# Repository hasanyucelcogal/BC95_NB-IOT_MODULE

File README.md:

# BC95_NB-IOT_MODULE
BC95 NB-IOT MODULE DESIGN. COMPATIBLE WITH QUECTEL BG96 LPWAN MODULE.

Front

Back

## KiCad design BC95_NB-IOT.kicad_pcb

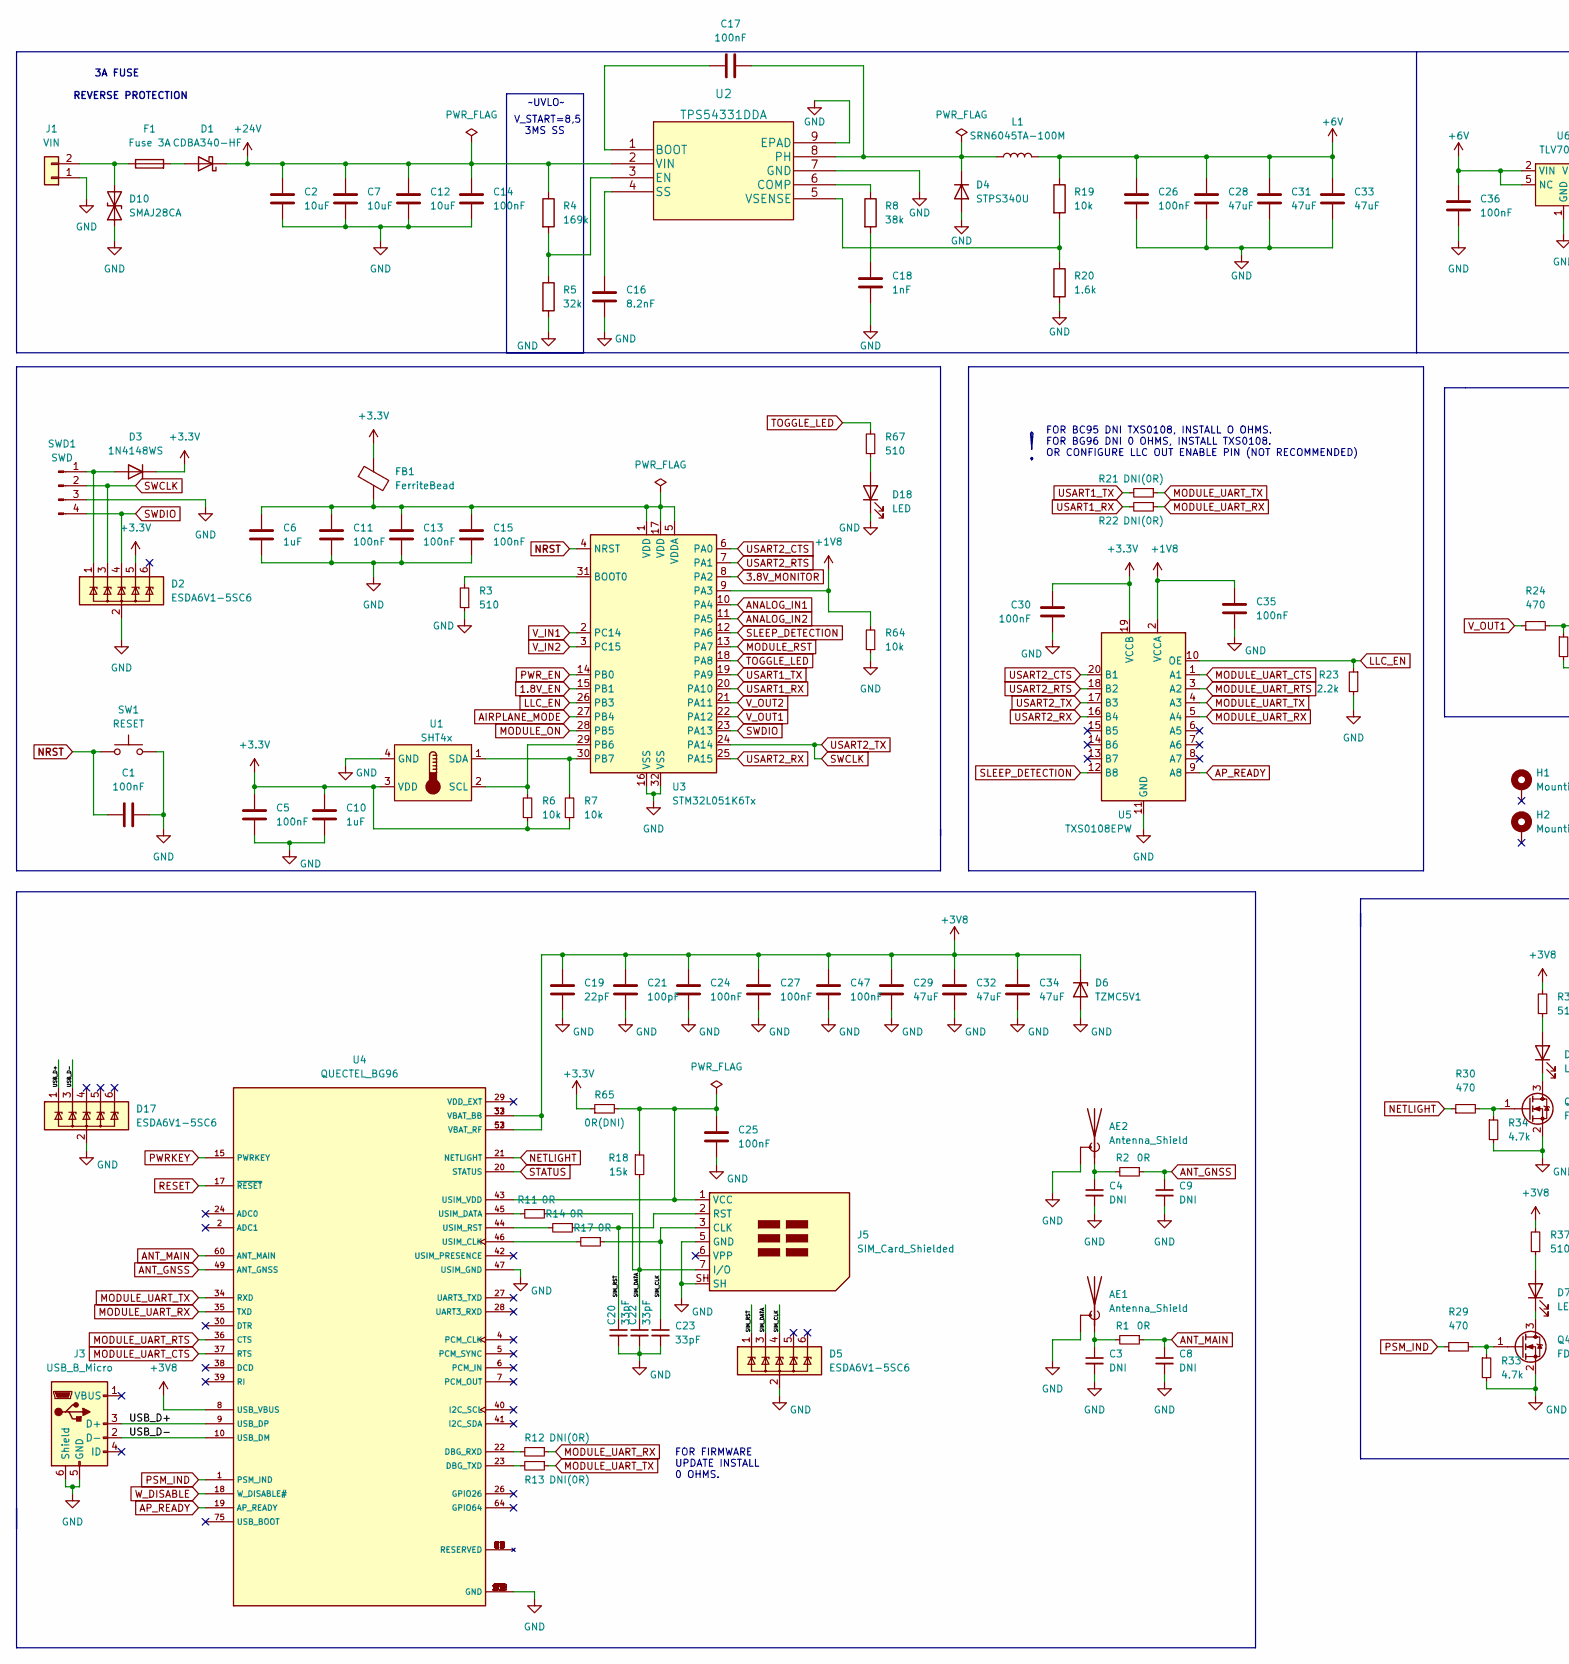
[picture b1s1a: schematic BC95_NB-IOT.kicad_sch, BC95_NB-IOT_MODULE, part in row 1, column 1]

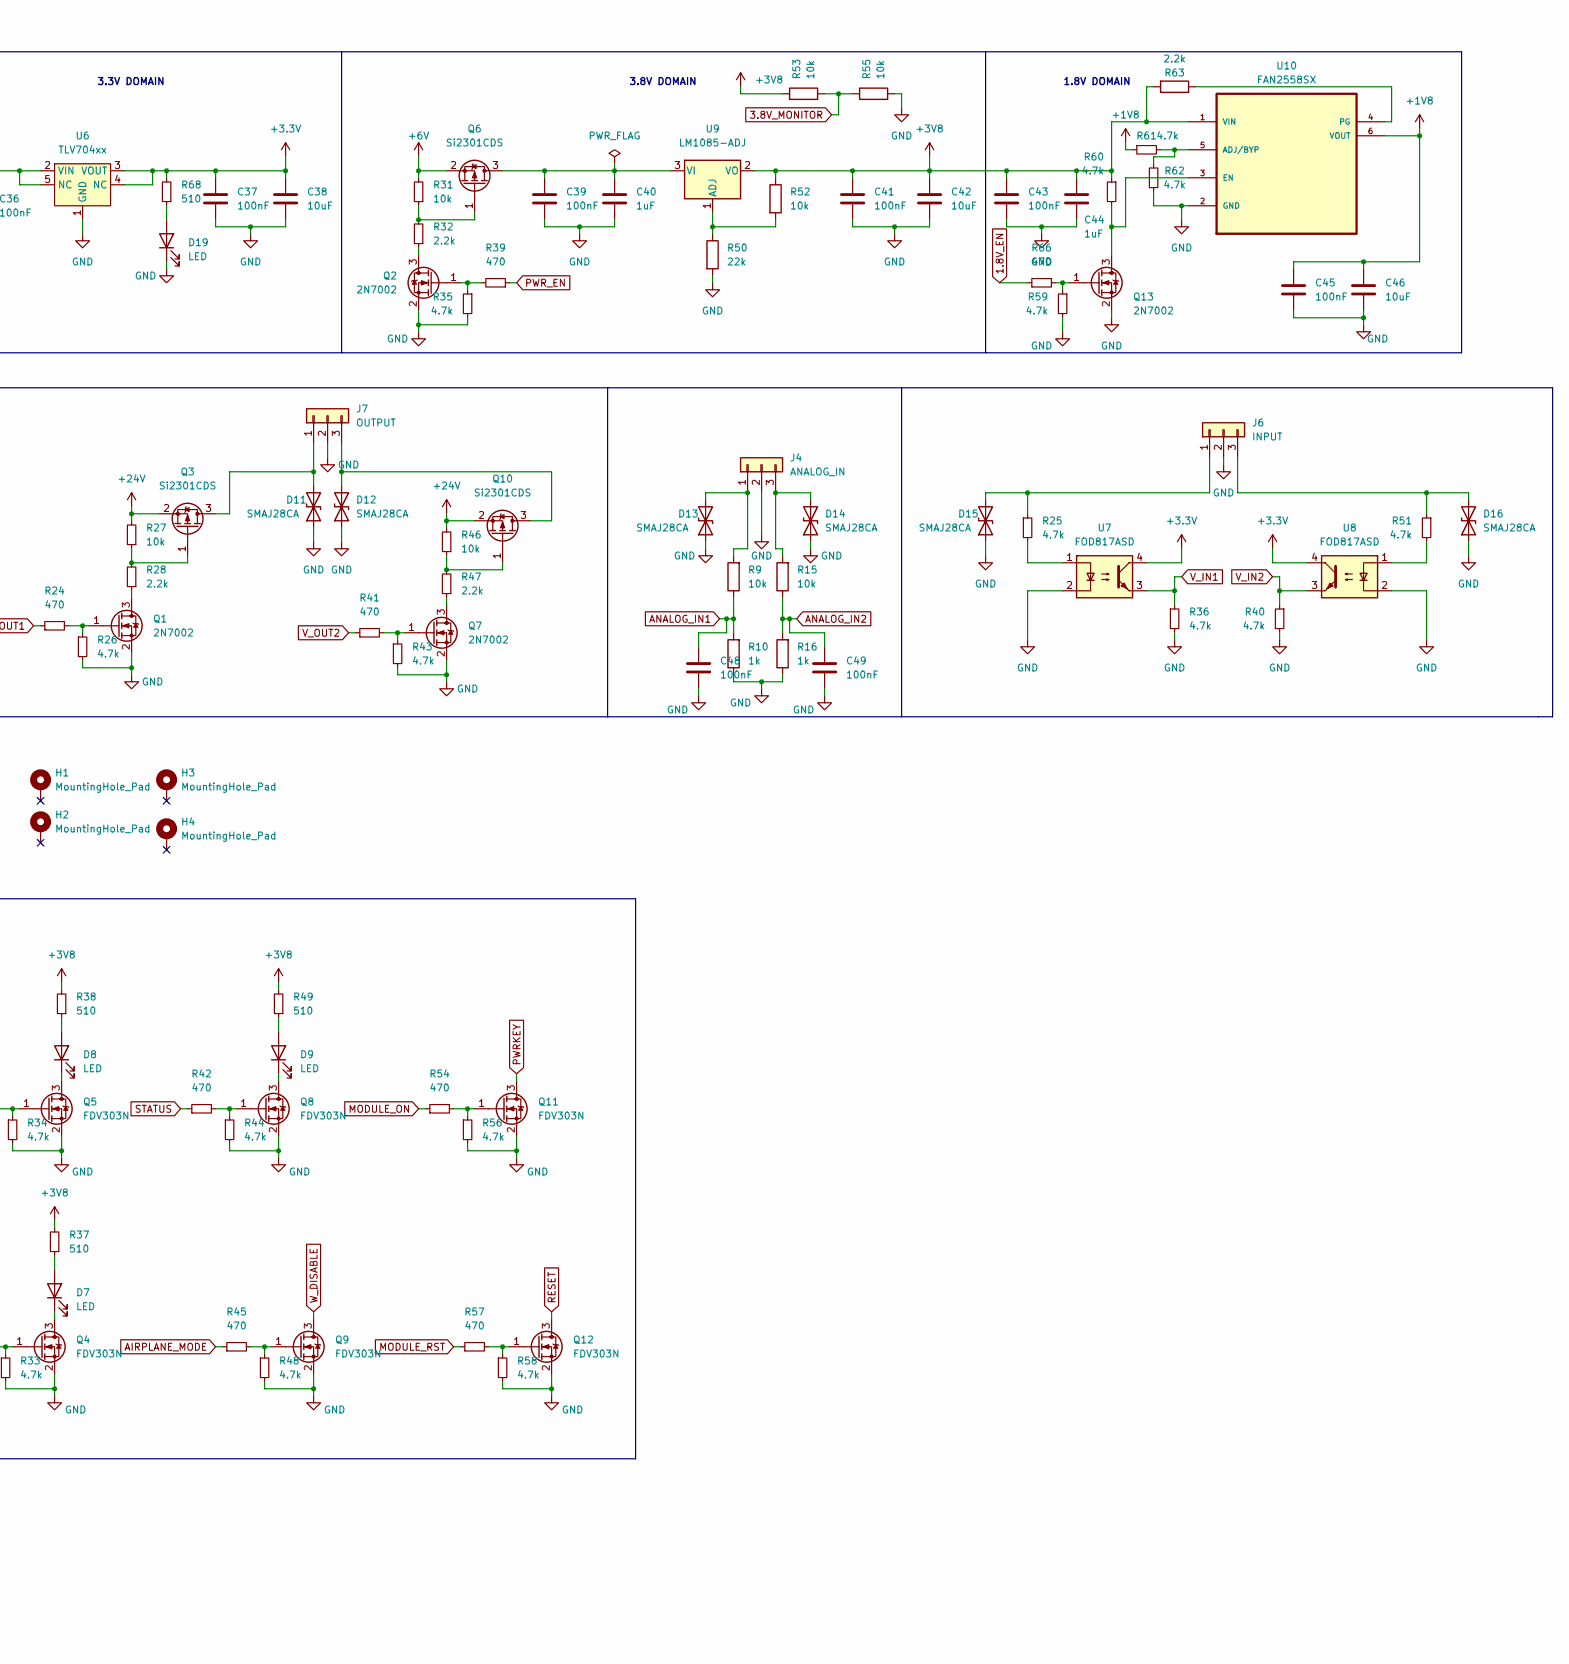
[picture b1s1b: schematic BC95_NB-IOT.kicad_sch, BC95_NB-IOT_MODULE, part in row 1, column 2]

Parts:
AE1, AE2: Antenna_Shield; SMA_Amphenol_901-144_Vertical
C1, C5, C11, C13, C15, C24, C25, C27, C30, C35, C36, C37, C39, C41, C43, C45, C47, C48, C49: 100nF; C_0603_1608Metric
C2, C7, C12: 10uF; C_1206_3216Metric_Pad1.33x1.80mm_HandSolder
C3, C4, C8, C9: DNI; C_0603_1608Metric
C6, C10, C40, C44: 1uF; C_0603_1608Metric
C14, C17, C26: 100nF; C_0603_1608Metric_Pad1.08x0.95mm_HandSolder
C16: 8.2nF; C_0603_1608Metric_Pad1.08x0.95mm_HandSolder
C18: 1nF; C_0603_1608Metric_Pad1.08x0.95mm_HandSolder
C19: 22pF; C_0603_1608Metric
C20, C22, C23: 33pF; C_0603_1608Metric
C21: 100pF; C_0603_1608Metric
C28, C31, C33: 47uF; CP_EIA-3528-21_Kemet-B_Pad1.50x2.35mm_HandSolder
C29, C32, C34: 47uF; CP_EIA-3528-21_Kemet-B
C38, C42, C46: 10uF; CP_EIA-3528-21_Kemet-B
D1: CDBA340-HF; D_SMA
D2, D5, D17: ESDA6V1-5SC6; SOT-23-6
D3: 1N4148WS; D_SOD-323
D4: STPS340U; D_SMB
D6: TZMC5V1; D_MiniMELF
D7, D8, D9, D18, D19: LED; LED_0603_1608Metric
D10, D11, D12, D13, D14, D15, D16: SMAJ28CA; D_SMA
F1: Fuse 3A; Fuse_Littelfuse-NANO2-451_453
FB1: FerriteBead; R_0603_1608Metric
H1, H2, H3, H4: MountingHole_Pad; MountingHole_3.2mm_M3_Pad_Via
J1: VIN; Altech_AK300_1x02_P5.00mm_45-Degree
J3: USB_B_Micro; USB_Micro-B_Molex_47346-0001
J4: ANALOG_IN; PhoenixContact_MC_1,5_3-G-3.81_1x03_P3.81mm_Horizontal
J5: SIM_Card_Shielded; ATTEND_MICRO_SIM
J6: INPUT; PhoenixContact_MC_1,5_3-G-3.81_1x03_P3.81mm_Horizontal
J7: OUTPUT; PhoenixContact_MC_1,5_3-G-3.81_1x03_P3.81mm_Horizontal
L1: SRN6045TA-100M; L_Bourns_SRN6045TA
Q1, Q2, Q7, Q13: 2N7002; SOT-23
Q3, Q6, Q10: Si2301CDS; SOT-23
Q4, Q5, Q8, Q9, Q11, Q12: FDV303N; SOT-23
R1, R2, R11, R14, R17: 0R; R_0603_1608Metric
R3, R37, R38, R49, R67, R68: 510; R_0603_1608Metric
R4: 169k; R_0603_1608Metric_Pad0.98x0.95mm_HandSolder
R5: 32k; R_0603_1608Metric_Pad0.98x0.95mm_HandSolder
R6, R7, R9, R15, R27, R31, R46, R52, R53, R55, R64: 10k; R_0603_1608Metric
R8: 38k; R_0603_1608Metric_Pad0.98x0.95mm_HandSolder
R10, R16: 1k; R_0603_1608Metric
R12, R13, R21, R22: DNI(0R); R_0603_1608Metric
R18: 15k; R_0603_1608Metric
R19: 10k; R_0603_1608Metric_Pad0.98x0.95mm_HandSolder
R20: 1.6k; R_0603_1608Metric_Pad0.98x0.95mm_HandSolder
R23, R28, R32, R47, R63: 2.2k; R_0603_1608Metric
R24, R29, R30, R39, R41, R42, R45, R54, R57, R66: 470; R_0603_1608Metric
R25, R26, R33, R34, R35, R36, R40, R43, R44, R48, R51, R56, R58, R59, R60, R61, R62: 4.7k; R_0603_1608Metric
R50: 22k; R_0603_1608Metric
R65: 0R(DNI); R_0603_1608Metric
SW1: RESET; SW_SPST_B3U-1000P
SWD1: SWD; PinHeader_1x04_P2.54mm_Vertical
U1: SHT4x; SHT4X
U2: TPS54331DDA; TI_SO-PowerPAD-8_ThermalVias
U3: STM32L051K6Tx; LQFP-32_7x7mm_P0.8mm
U4: QUECTEL_BG96; XCVR_BG96
U5: TXS0108EPW; TSSOP-20_4.4x6.5mm_P0.65mm
U6: TLV704xx; SOT-23-5
U7, U8: FOD817ASD; SMDIP-4_W9.53mm
U9: LM1085-ADJ; TO-263-3_TabPin2
U10: FAN2558SX; SOT-23-6

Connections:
1.8V_EN: R66.1, U3.15 (PB1)
3.8V_MONITOR: R53.2, R55.1, U3.8 (PA2)
+1V8: C35.1, C45.1, C46.1, R61.1, R64.2, U3.9 (PA3), U5.2 (VCCA), U10.6 (VOUT)
+3V3: C5.1, C10.1, C30.1, C37.1, C38.1, D2.5 (IO4), D3.1 (K), FB1.1, R6.1, R7.1, R65.1, R68.2, U1.3 (VDD), U5.19 (VCCB), U6.3 (VOUT), U6.4 (NC), U7.4, U8.4
+3V8: C19.1, C21.1, C24.1, C27.1, C29.1, C32.1, C34.1, C41.1, C42.1, C43.1, C44.1, C47.1, D6.1 (K), R37.2, R38.2, R49.2, R52.1, R53.1, R60.1, R63.2, U4.8 (USB_VBUS), U4.32 (VBAT_BB), U4.33 (VBAT_BB), U4.52 (VBAT_RF), U4.53 (VBAT_RF), U9.2 (VO), U10.1 (VIN)
+6V: C26.2, C28.2, C31.2, C33.2, C36.1, L1.2, Q6.2 (S), R19.1, R31.2, U6.2 (VIN), U6.5 (NC)
+24V: C2.1, C7.1, C12.1, C14.2, D1.1 (K), Q3.2 (S), Q10.2 (S), R4.1, R27.2, R46.2, U2.2 (VIN)
/SIM_CLK: C23.1, D5.4 (IO3), J5.3 (CLK), R17.1
/SIM_DATA: C22.1, D5.3 (IO2), J5.7 (I/O), R11.1, R18.2
/SIM_RST: C20.1, D5.1 (IO1), J5.2 (RST), R14.1
/USB_D+: D17.1 (IO1), J3.3 (D+), U4.9 (USB_DP)
/USB_D-: D17.3 (IO2), J3.2 (D-), U4.10 (USB_DM)
AIRPLANE_MODE: R45.1, U3.27 (PB4)
ANALOG_IN1: C48.1, R9.1, R10.2, U3.10 (PA4)
ANALOG_IN2: C49.1, R15.1, R16.2, U3.11 (PA5)
ANT_GNSS: C9.1, R2.1, U4.49 (ANT_GNSS)
ANT_MAIN: C8.1, R1.1, U4.60 (ANT_MAIN)
AP_READY: U4.19 (AP_READY), U5.9 (A8)
GND: AE1.2 (Shield), AE2.2 (Shield), C1.2, C2.2, C3.2, C4.2, C5.2, C6.2, C7.2, C8.2, C9.2, C10.2, C11.2, C12.2, C13.2, C14.1, C15.2, C16.1, C18.1, C19.2, C20.2, C21.2, C22.2, C23.2, C24.2, C25.2, C26.1, C27.2, C28.1, C29.2, C30.2, C31.1, C32.2, C33.1, C34.2, C35.2, C36.2, C37.2, C38.2, C39.2, C40.2, C41.2, C42.2, C43.2, C44.2, C45.2, C46.2, C47.2, C48.2, C49.2, D2.2 (GND), D4.2 (A), D5.2 (GND), D6.2 (A), D10.1 (A1), D11.1 (A1), D12.1 (A1), D13.1 (A1), D14.1 (A1), D15.1 (A1), D16.1 (A1), D17.2 (GND), D18.1 (K), D19.1 (K), J1.1, J3.5 (GND), J3.6 (Shield), J4.2, J5.5 (GND), J5.SH, J6.2, J7.2, Q1.2 (S), Q2.2 (S), Q4.2 (S), Q5.2 (S), Q7.2 (S), Q8.2 (S), Q9.2 (S), Q11.2 (S), Q12.2 (S), Q13.2 (S), R3.1, R5.2, R10.1, R16.1, R20.2, R23.2, R26.2, R33.2, R34.2, R35.2, R36.2, R40.2, R43.2, R44.2, R48.2, R50.2, R55.2, R56.2, R58.2, R59.2, R62.1, R64.1, SW1.2, SWD1.3, U1.4 (GND), U2.7 (GND), U2.9 (EPAD), U3.16 (VSS), U3.32 (VSS), U4.3 (GND), U4.31 (GND), U4.47 (USIM_GND), U4.48 (GND), U4.50 (GND), U4.54 (GND), U4.55 (GND), U4.58 (GND), U4.59 (GND), U4.61 (GND), U4.62 (GND), U4.67 (GND), U4.68 (GND), U4.69 (GND), U4.70 (GND), U4.71 (GND), U4.72 (GND), U4.73 (GND), U4.74 (GND), U4.79 (GND), U4.80 (GND), U4.81 (GND), U4.82 (GND), U4.89 (GND), U4.90 (GND), U4.91 (GND), U4.100 (GND), U4.101 (GND), U4.102 (GND), U5.11 (GND), U6.1 (GND), U7.2, U8.2, U10.2 (GND)
LLC_EN: R23.1, U3.26 (PB3), U5.10 (OE)
MODULE_ON: R54.1, U3.28 (PB5)
MODULE_RST: R57.1, U3.13 (PA7)
MODULE_UART_CTS: U4.37 (RTS), U5.1 (A1)
MODULE_UART_RTS: U4.36 (CTS), U5.3 (A2)
MODULE_UART_RX: R12.1, R22.1, U4.35 (TXD), U5.5 (A4)
MODULE_UART_TX: R13.1, R21.1, U4.34 (RXD), U5.4 (A3)
NETLIGHT: R30.1, U4.21 (NETLIGHT)
NRST: C1.1, SW1.1, U3.4 (NRST)
unnamed: AE1.1 (A), C3.1, R1.2
unnamed: AE2.1 (A), C4.1, R2.2
unnamed: C6.1, C11.1, C13.1, C15.1, FB1.2, U3.1 (VDD), U3.5 (VDDA), U3.17 (VDD)
unnamed: C16.2, U2.4 (SS)
unnamed: C17.1, U2.1 (BOOT)
unnamed: C17.2, D4.1 (K), L1.1, U2.8 (PH)
unnamed: C18.2, R8.2
unnamed: C25.1, J5.1 (VCC), R18.1, R65.2, U4.43 (USIM_VDD)
unnamed: C39.1, C40.1, Q6.3 (D), U9.3 (VI)
unnamed: D1.2 (A), F1.2
unnamed: D2.1 (IO1), D3.2 (A), SWD1.1
unnamed: D7.1 (K), Q4.3 (D)
unnamed: D7.2 (A), R37.1
unnamed: D8.1 (K), Q5.3 (D)
unnamed: D8.2 (A), R38.1
unnamed: D9.1 (K), Q8.3 (D)
unnamed: D9.2 (A), R49.1
unnamed: D10.2 (A2), F1.1, J1.2
unnamed: D11.2 (A2), J7.1, Q3.3 (D)
unnamed: D12.2 (A2), J7.3, Q10.3 (D)
unnamed: D13.2 (A2), J4.1, R9.2
unnamed: D14.2 (A2), J4.3, R15.2
unnamed: D15.2 (A2), J6.1, R25.1
unnamed: D16.2 (A2), J6.3, R51.1
unnamed: D18.2 (A), R67.1
unnamed: D19.2 (A), R68.1
unnamed: Q1.1 (G), R24.2, R26.1
unnamed: Q1.3 (D), R28.1
unnamed: Q2.1 (G), R35.1, R39.2
unnamed: Q2.3 (D), R32.1
unnamed: Q3.1 (G), R27.1, R28.2
unnamed: Q4.1 (G), R29.2, R33.1
unnamed: Q5.1 (G), R30.2, R34.1
unnamed: Q6.1 (G), R31.1, R32.2
unnamed: Q7.1 (G), R41.2, R43.1
unnamed: Q7.3 (D), R47.1
unnamed: Q8.1 (G), R42.2, R44.1
unnamed: Q9.1 (G), R45.2, R48.1
unnamed: Q10.1 (G), R46.1, R47.2
unnamed: Q11.1 (G), R54.2, R56.1
unnamed: Q12.1 (G), R57.2, R58.1
unnamed: Q13.1 (G), R59.1, R66.2
unnamed: Q13.3 (D), R60.2, U10.3 (EN)
unnamed: R3.2, U3.31 (BOOT0)
unnamed: R4.2, R5.1, U2.3 (EN)
unnamed: R6.2, U1.2 (SCL), U3.29 (PB6)
unnamed: R7.2, U1.1 (SDA), U3.30 (PB7)
unnamed: R8.1, U2.6 (COMP)
unnamed: R11.2, U4.45 (USIM_DATA)
unnamed: R12.2, U4.22 (DBG_RXD)
unnamed: R13.2, U4.23 (DBG_TXD)
unnamed: R14.2, U4.44 (USIM_RST)
unnamed: R17.2, U4.46 (USIM_CLK)
unnamed: R19.2, R20.1, U2.5 (VSENSE)
unnamed: R25.2, U7.1
unnamed: R50.1, R52.2, U9.1 (ADJ)
unnamed: R51.2, U8.1
unnamed: R61.2, R62.2, U10.5 (ADJ/BYP)
unnamed: R63.1, U10.4 (PG)
PSM_IND: R29.1, U4.1 (PSM_IND)
PWRKEY: Q11.3 (D), U4.15 (PWRKEY)
PWR_EN: R39.1, U3.14 (PB0)
RESET: Q12.3 (D), U4.17 (~RESET)
SLEEP_DETECTION: U3.12 (PA6), U5.12 (B8)
STATUS: R42.1, U4.20 (STATUS)
SWCLK: D2.3 (IO2), SWD1.2, U3.24 (PA14), U5.17 (B3)
SWDIO: D2.4 (IO3), SWD1.4, U3.23 (PA13)
TOGGLE_LED: R67.2, U3.18 (PA8)
USART1_RX: R22.2, U3.20 (PA10)
USART1_TX: R21.2, U3.19 (PA9)
USART2_CTS: U3.6 (PA0), U5.20 (B1)
USART2_RTS: U3.7 (PA1), U5.18 (B2)
USART2_RX: U3.25 (PA15), U5.16 (B4)
V_IN1: R36.1, U3.2 (PC14), U7.3
V_IN2: R40.1, U3.3 (PC15), U8.3
V_OUT1: R24.1, U3.22 (PA12)
V_OUT2: R41.1, U3.21 (PA11)
W_DISABLE: Q9.3 (D), U4.18 (W_DISABLE#)

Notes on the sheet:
FOR BC95 DNI TXS0108, INSTALL O OHMS. FOR BG96 DNI 0 OHMS, INSTALL TXS0108. OR CONFIGURE LLC OUT ENABLE PIN (NOT RECOMMENDED)
FOR FIRMWARE UPDATE INSTALL 0 OHMS.
V_START=8,5 3MS SS
1.8V DOMAIN
~UVLO~
3.3V DOMAIN
3A FUSE REVERSE PROTECTION
3.8V DOMAIN

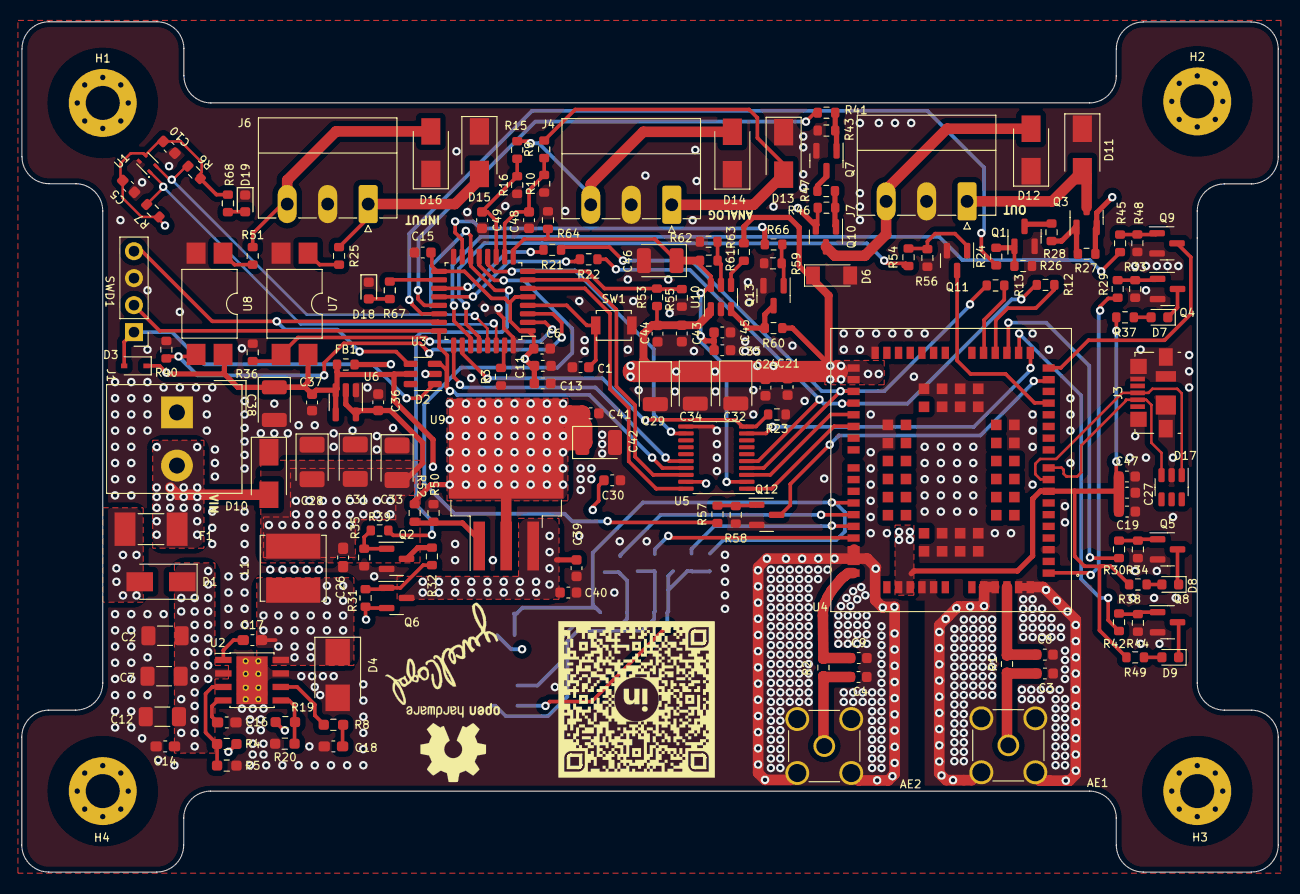
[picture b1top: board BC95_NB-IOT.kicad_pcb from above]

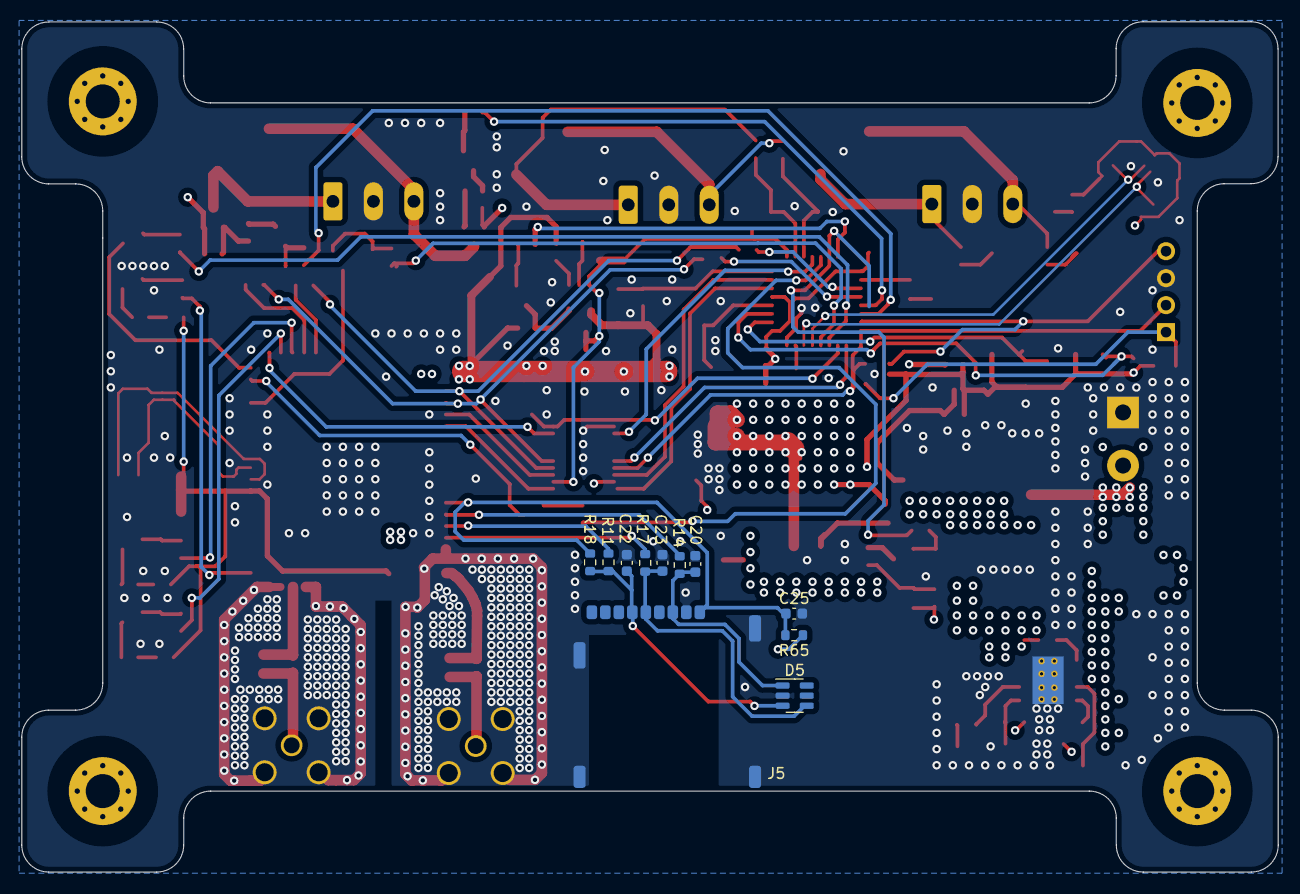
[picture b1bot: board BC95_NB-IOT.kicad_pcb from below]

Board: 4 copper layers, 118.3 x 80.0 mm, 176 parts (11 on the bottom side), 106 nets.

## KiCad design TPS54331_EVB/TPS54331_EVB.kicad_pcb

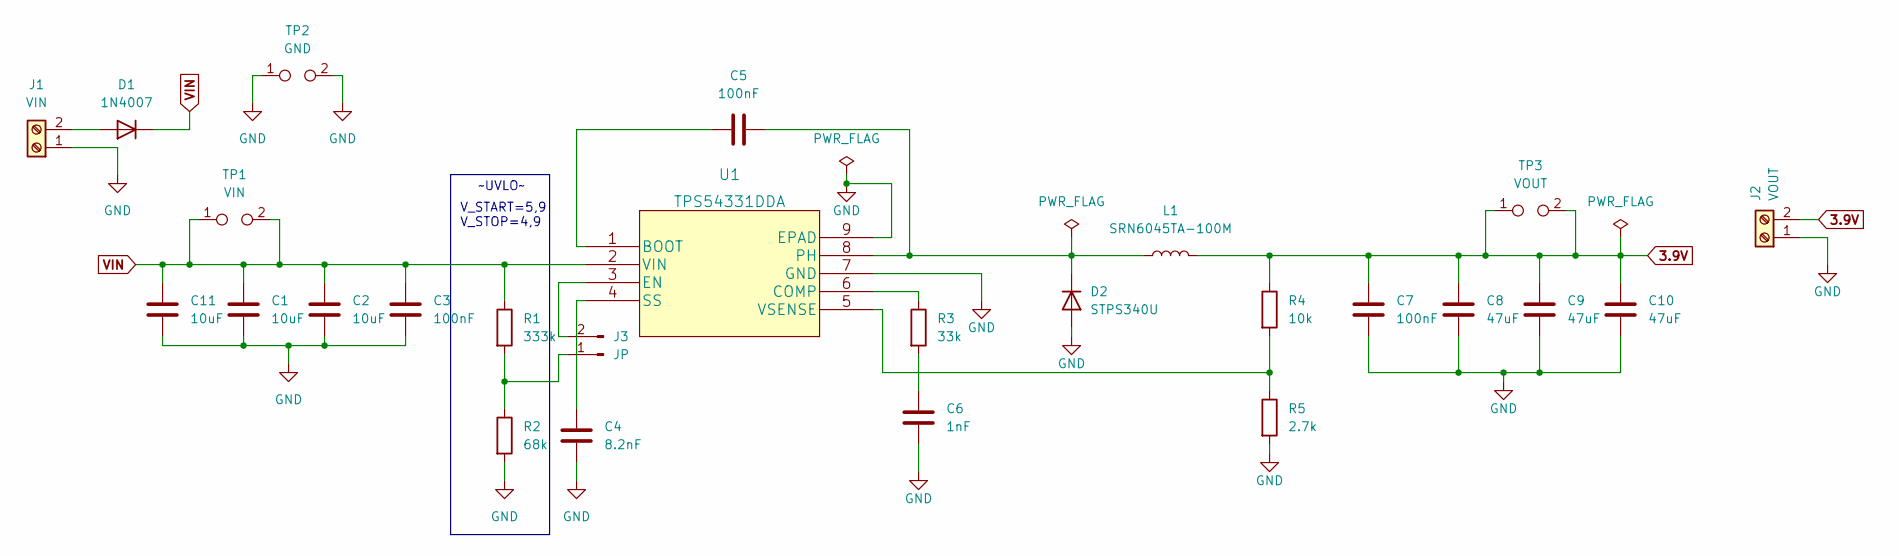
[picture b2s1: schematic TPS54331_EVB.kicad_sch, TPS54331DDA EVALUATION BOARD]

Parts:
C1, C2, C11: 10uF; C_1206_3216Metric_Pad1.33x1.80mm_HandSolder
C3, C5, C7: 100nF; C_0603_1608Metric_Pad1.08x0.95mm_HandSolder
C4: 8.2nF; C_0603_1608Metric_Pad1.08x0.95mm_HandSolder
C6: 1nF; C_0603_1608Metric_Pad1.08x0.95mm_HandSolder
C8, C9, C10: 47uF; CP_EIA-3528-21_Kemet-B_Pad1.50x2.35mm_HandSolder
D1: 1N4007; D_SMA
D2: STPS340U; D_SMB
J1: VIN; TerminalBlock_MetzConnect_Type086_RT03402HBLC_1x02_P3.81mm_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
J2: VOUT; TerminalBlock_MetzConnect_Type086_RT03402HBLC_1x02_P3.81mm_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
J3: JP; PinHeader_1x02_P2.54mm_Vertical
L1: SRN6045TA-100M; L_Bourns_SRN6045TA
R1: 333k; R_0603_1608Metric_Pad0.98x0.95mm_HandSolder
R2: 68k; R_0603_1608Metric_Pad0.98x0.95mm_HandSolder
R3: 33k; R_0603_1608Metric_Pad0.98x0.95mm_HandSolder
R4: 10k; R_0603_1608Metric_Pad0.98x0.95mm_HandSolder
R5: 2.7k; R_0603_1608Metric_Pad0.98x0.95mm_HandSolder
TP1: VIN; TestPoint_2Pads_Pitch2.54mm_Drill0.8mm
TP2: GND; TestPoint_2Pads_Pitch2.54mm_Drill0.8mm
TP3: VOUT; TestPoint_2Pads_Pitch2.54mm_Drill0.8mm
U1: TPS54331DDA; TI_SO-PowerPAD-8_ThermalVias

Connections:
3.9V: C7.2, C8.2, C9.2, C10.2, J2.2, L1.2, R4.1, TP3.1, TP3.2
GND: C1.2, C2.2, C3.1, C4.1, C6.1, C7.1, C8.1, C9.1, C10.1, C11.2, D2.2 (A), J1.1, J2.1, R2.2, R5.2, TP2.1, TP2.2, U1.7 (GND), U1.9 (EPAD)
unnamed: C4.2, U1.4 (SS)
unnamed: C5.1, U1.1 (BOOT)
unnamed: C5.2, D2.1 (K), L1.1, U1.8 (PH)
unnamed: C6.2, R3.2
unnamed: D1.2 (A), J1.2
unnamed: J3.1, R1.2, R2.1
unnamed: R3.1, U1.6 (COMP)
unnamed: R4.2, R5.1, U1.5 (VSENSE)
unnamed: J3.2, U1.3 (EN)
VIN: C1.1, C2.1, C3.2, C11.1, D1.1 (K), R1.1, TP1.1, TP1.2, U1.2 (VIN)

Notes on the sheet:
V_START=5,9 V_STOP=4,9
~UVLO~

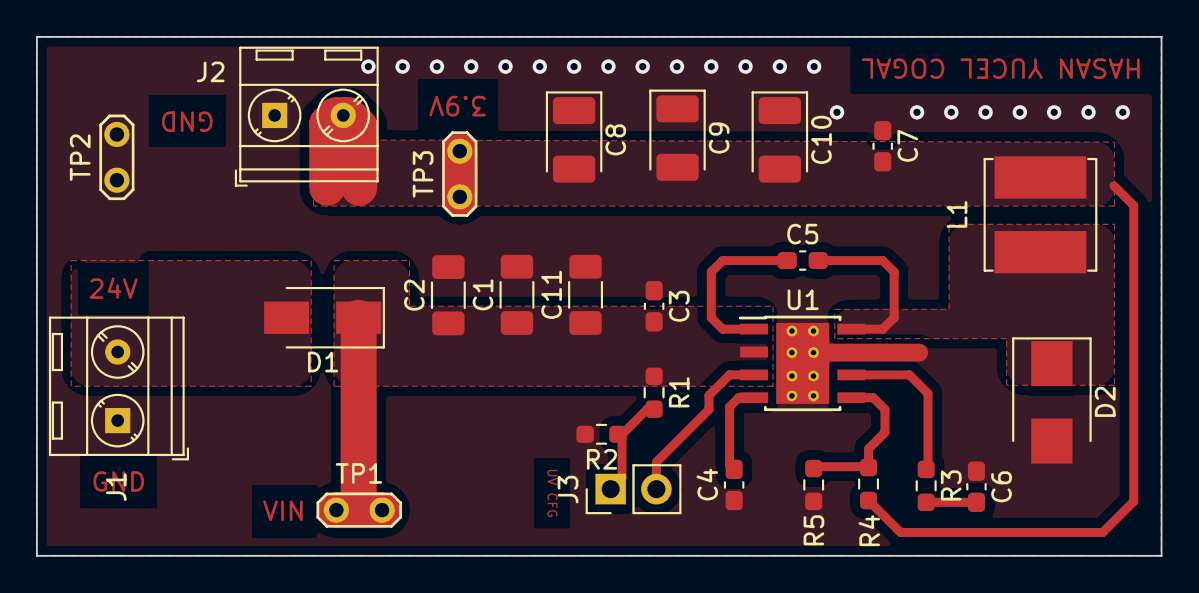
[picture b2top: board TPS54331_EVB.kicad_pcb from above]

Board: 2 copper layers, 62.5 x 28.8 mm, 26 parts (0 on the bottom side), 12 nets.

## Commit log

2022-05-12 BC95 NB-IOT Module CAD
2022-05-13 commit changes
2022-05-15 new commit
2022-05-19 new updates
    placing and routing
2022-05-20 placement and routing
2022-05-21 routing
2022-05-24 board layout
2022-05-24 directory update
2022-05-25 3d models added.
